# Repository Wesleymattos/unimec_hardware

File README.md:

# unimec_hardware
Desenvolvimento do hardware da unimec

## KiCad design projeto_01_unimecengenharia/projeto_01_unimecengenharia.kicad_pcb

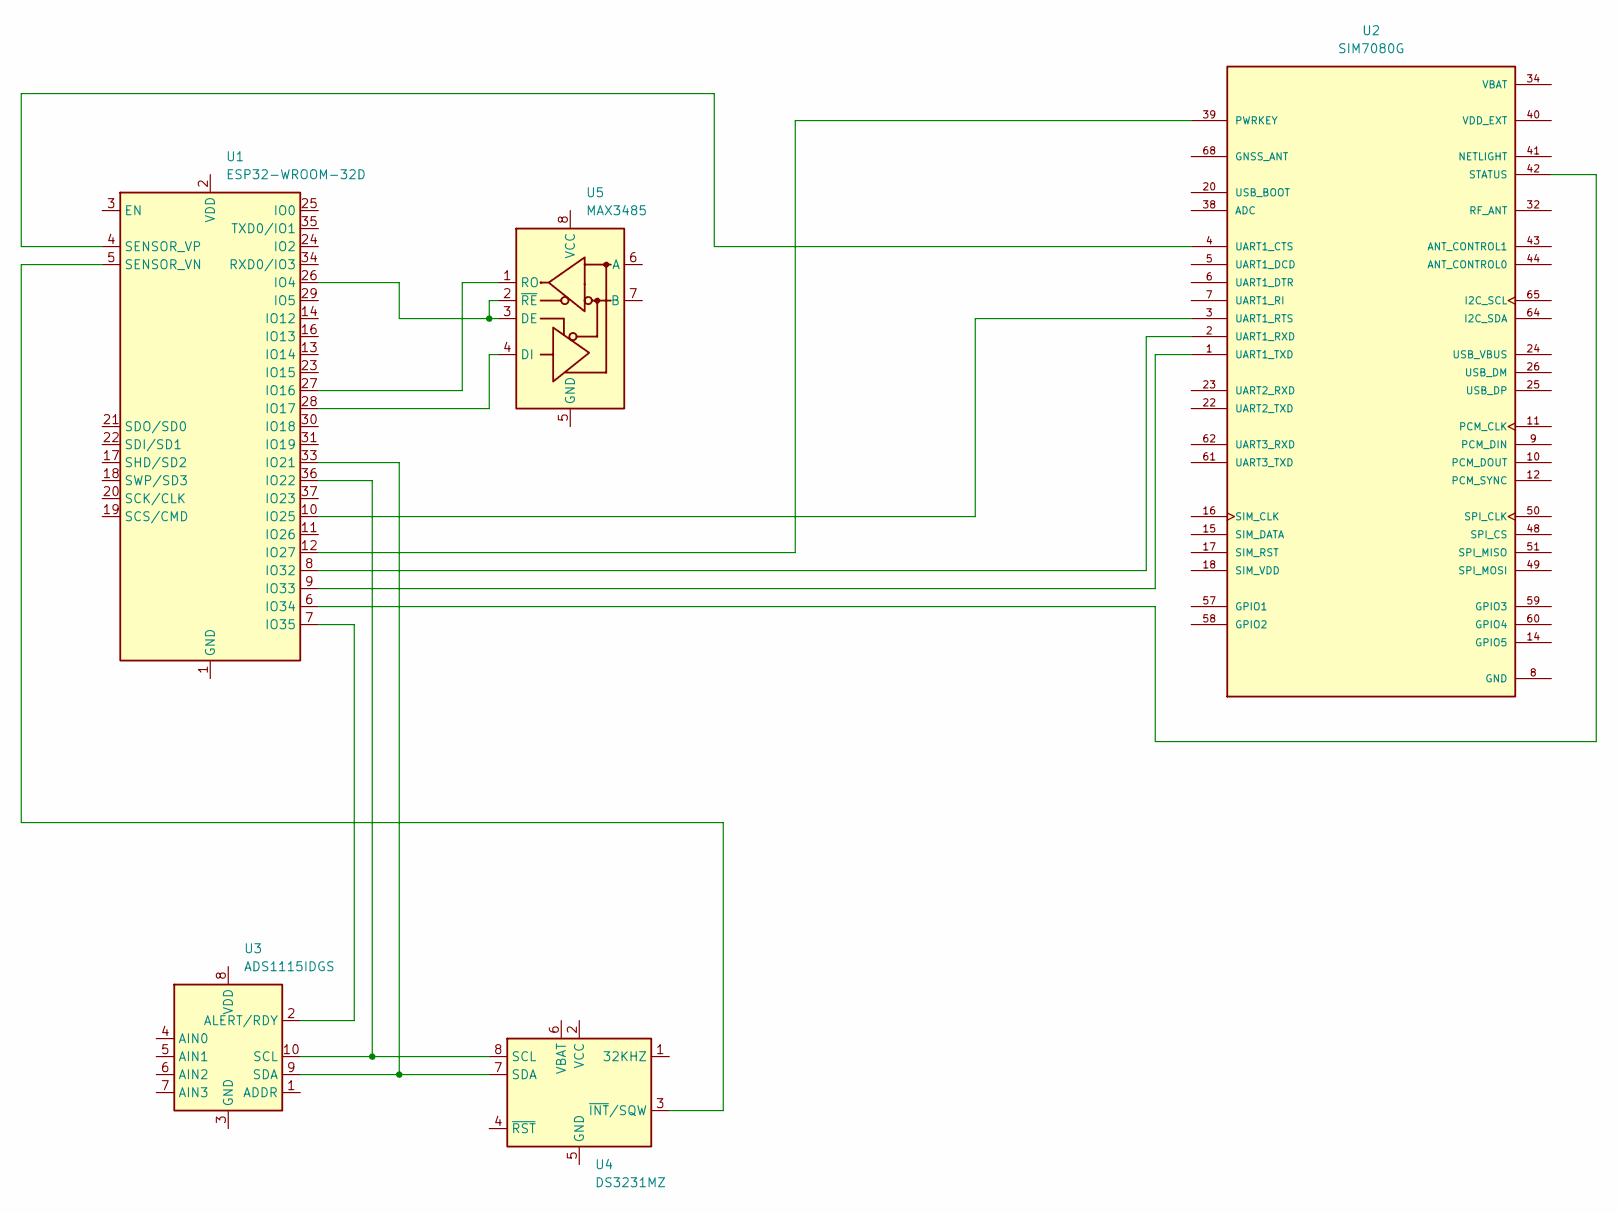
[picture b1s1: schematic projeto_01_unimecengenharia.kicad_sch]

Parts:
U1: ESP32-WROOM-32D
U2: SIM7080G; XCVR_SIM7080G; PARTREV 1.04
U3: ADS1115IDGS; TSSOP-10_3x3mm_P0.5mm
U4: DS3231MZ; SOIC-8_3.9x4.9mm_P1.27mm
U5: MAX3485; SOIC-8_3.9x4.9mm_P1.27mm

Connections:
GND: U2.8 (GND), U2.13 (GND), U2.19 (GND), U2.21 (GND), U2.27 (GND), U2.30 (GND), U2.31 (GND), U2.33 (GND), U2.36 (GND), U2.37 (GND), U2.45 (GND), U2.63 (GND), U2.66 (GND), U2.67 (GND), U2.69 (GND), U2.70 (GND), U2.71 (GND), U2.72 (GND), U2.73 (GND), U2.74 (GND), U2.75 (GND), U2.76 (GND), U2.77 (GND)
unnamed: U1.1 (GND), U1.15 (GND), U1.38 (GND), U1.39 (GND)
unnamed: U1.26 (IO4), U5.2 (~RE), U5.3 (DE)
unnamed: U1.27 (IO16), U5.1 (RO)
unnamed: U1.28 (IO17), U5.4 (DI)
unnamed: U1.33 (IO21), U3.9 (SDA), U4.7 (SDA)
unnamed: U1.36 (IO22), U3.10 (SCL), U4.8 (SCL)
unnamed: U1.10 (IO25), U2.3 (UART1_RTS)
unnamed: U1.12 (IO27), U2.39 (PWRKEY)
unnamed: U1.8 (IO32), U2.2 (UART1_RXD)
unnamed: U1.9 (IO33), U2.1 (UART1_TXD)
unnamed: U1.6 (IO34), U2.42 (STATUS)
unnamed: U1.7 (IO35), U3.2 (ALERT/RDY)
unnamed: U1.5 (SENSOR_VN), U4.3 (~INT/SQW)
unnamed: U1.4 (SENSOR_VP), U2.4 (UART1_CTS)
VBAT: U2.34 (VBAT), U2.35 (VBAT)

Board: 2 copper layers, 5 parts (0 on the bottom side), 16 nets, no tracks yet.
